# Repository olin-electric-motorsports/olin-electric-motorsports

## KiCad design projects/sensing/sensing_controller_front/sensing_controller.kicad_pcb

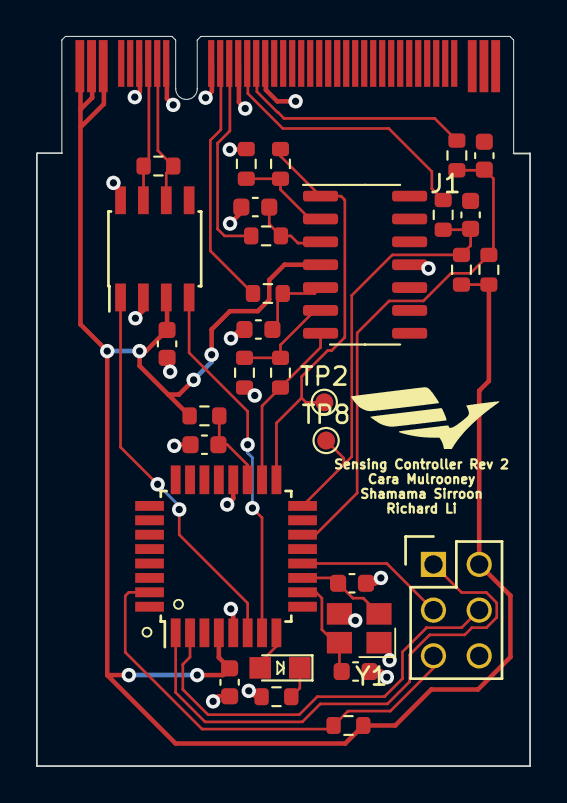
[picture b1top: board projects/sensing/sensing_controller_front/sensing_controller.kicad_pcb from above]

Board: 2 copper layers, 27.4 x 40.5 mm, 32 parts (0 on the bottom side), 27 nets.

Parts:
C1, C3, C6, C8, C9, C10: C_0.1uF; C_0603
C2: C_100pF; C_0603
C4, C5: C_30pF; C_0603
D1: LED_0805; LED_0805_OEM
J1: Automotive_M.2_Edge_Connector
J2: CONN_02X03; Pin_Header_Straight_2x03
R1, R4, R6, R14: R_100; R_0603
R2: R_120_DNP; R_0603
R3: R_10K; R_0603
R5, R11: R_200; R_0603
R7, R8, R9, R10: 100R; R_0603
R12, R13: R_1000_DNP; R_0603
TP2, TP8: TestPoint; TestPoint_Pad_D1.0mm
U1: MCP2561-E_SN; SOIC-8_3.9x4.9mm_Pitch1.27mm_OEM
U2: ATMEGA16M1; TQFP-32_7x7mm_Pitch0.8mm
U4: AD8630; SOIC-14_3.9x8.7mm_P1.27mm
Y1: Crystal_SMD; Crystal_SMD_FA238

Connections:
+5V: C1.1, C3.1, J1.P1, J1.P2, J1.P3, J2.2, R1.1, R3.1, R12.2, R13.2, U1.3 (VDD), U2.4 (VCC), U4.4 (V+)
/CAN_+: J1.7, R2.1, U1.7 (CANH)
/CAN_-: J1.8, R2.2, U1.6 (CANL)
/CAN_RX: U1.4 (RXD), U2.7 ((PCINT11/T1/ICP1B/RXCAN)PC3)
/CAN_TX: U1.1 (TXD), U2.6 ((PCINT10/T0/TXCAN)PC2)
/DEBUG_LED: D1.2 (A), U2.8 ((PCINT0/MISO/PSCOUT2A)PB0)
/MISO: J2.1, U2.1 ((PCINT18/PSCIN2/OC1A/MISO_A)PD2)
/MOSI: J2.4, U2.2 ((PCINT19/TXD/TXLIN/OC0A/~SS/MOSI_A)PD3)
/RESET: J2.5, R3.2, U2.31 ((PCINT24/OCD/~RESET)PE0)
/SCK: J2.3, U2.12 ((PCINT20/ADC1/RXD/RXLIN/ICP1A/SCK_A)PD4)
/lp1_Vout: J1.11, R8.1
/lp1_fVout: R14.1, U2.18 ((PCINT13/ADC9/ACMP3/AMP1+)PC5), U4.7
/lp2_Vout: J1.12, R7.1
/lp2_fVout: R6.1, TP2.1, U2.17 ((PCINT12/ADC8/ACMPN3/AMP1-)PC4), U4.1
/ws1_Vout: J1.14, R10.1
/ws1_fVout: C10.1, R10.2, R13.1, TP8.1, U2.16 ((PCINT2/ADC5/INT1/ACMPN0)PB2)
/ws2_Vout: J1.15, R9.1
/ws2_fVout: C9.1, R9.2, R12.1, U2.14 ((PCINT22/ADC3/INT0/ACMPN2)PD6)
GND: C1.2, C2.2, C3.2, C4.2, C5.2, C6.2, C8.2, C9.2, C10.2, J1.6, J1.9, J1.10, J1.13, J1.16, J2.6, R4.2, R5.1, R11.1, U1.2 (VSS), U1.8 (STBY), U2.5 (GND), U2.20 (AGND), U4.11 (V-), Y1.2, Y1.4
unnamed: C2.1, R1.2, U2.19 (AVCC)
unnamed: C4.1, U2.11 ((PCINT26/ADC0/XTAL2)PE2), Y1.1
unnamed: C5.1, U2.10 ((PCINT25/OC0B/XTAL1)PE1), Y1.3
unnamed: C6.1, R7.2, U4.3 (+)
unnamed: C8.1, R8.2, U4.5 (+)
unnamed: D1.1 (K), R4.1
unnamed: R5.2, R6.2, U4.2 (-)
unnamed: R11.2, R14.2, U4.6 (-)

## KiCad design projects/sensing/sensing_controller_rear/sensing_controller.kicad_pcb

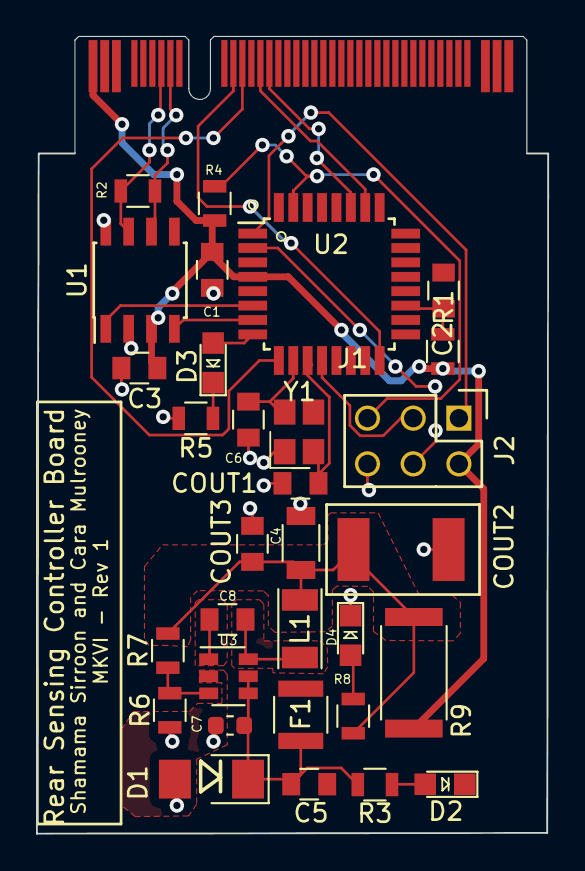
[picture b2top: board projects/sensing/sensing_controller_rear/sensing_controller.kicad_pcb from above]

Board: 2 copper layers, 28.4 x 44.3 mm, 32 parts (0 on the bottom side), 26 nets.

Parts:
C1, C3, C5, C8: C_0.1uF; C_0805_OEM
C2: C_100pF; C_0805_OEM
C4, C6: C_30pF; C_0805_OEM
C7: C_2.2uF; C_0603_1608Metric
COUT1: C_22uF; C_1206_OEM
COUT2: C_33uF; Fuse_1812
COUT3: C_47uF; C_0805_OEM
D1: D_Zener_18V; DO-214AA
D2, D3, D4: LED_0805; LED_0805_OEM
F1: F_500mA_16V; Fuse_1210
J1: Automotive_M.2_Edge_Connector
J2: CONN_02X03; Pin_Header_Straight_2x03
L1: L_100uH; L_100uH_OEM
R1, R5: R_100; R_0805_OEM
R2: R_120_DNP; R_0805_OEM
R3: R_1K; R_0805_OEM
R4: R_10K; R_0805_OEM
R6: R_25K; R_0805_OEM
R7: R_100K; R_0805_OEM
R8: R_200; R_0805_OEM
R9: R_0_2512; R_2512_OEM
U1: MCP2561-E_SN; SOIC-8_3.9x4.9mm_Pitch1.27mm_OEM
U2: ATMEGA16M1; TQFP-32_7x7mm_Pitch0.8mm
U3: TPS560430YF; SOT-23-6_OEM
Y1: Crystal_SMD; Crystal_SMD_FA238

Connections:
+5V: C1.1, C3.1, J1.P1, J2.2, R1.1, R4.1, R9.1, U1.3 (VDD), U2.4 (VCC)
/CAN_+: J1.7, R2.1, U1.7 (CANH)
/CAN_-: J1.8, R2.2, U1.6 (CANL)
/CAN_RX: U1.4 (RXD), U2.7 ((PCINT11/T1/ICP1B/RXCAN)PC3)
/CAN_TX: U1.1 (TXD), U2.6 ((PCINT10/T0/TXCAN)PC2)
/MISO: J2.1, U2.1 ((PCINT18/PSCIN2/OC1A/MISO_A)PD2)
/MOSI: J2.4, U2.2 ((PCINT19/TXD/TXLIN/OC0A/~SS/MOSI_A)PD3)
/RESET: J2.5, R4.2, U2.31 ((PCINT24/OCD/~RESET)PE0)
/SCK: J2.3, U2.12 ((PCINT20/ADC1/RXD/RXLIN/ICP1A/SCK_A)PD4)
/lp1_Vout: J1.14, U2.26 ((PCINT5/ADC6/INT2/ACMPN1/AMP2-)PB5)
/lp2_Vout: J1.15, U2.27 ((PCINT6/ADC7/PSCOUT1B)PB6)
/ws1_Vout: J1.11, U2.16 ((PCINT2/ADC5/INT1/ACMPN0)PB2)
/ws2_Vout: J1.12, U2.9 ((PCINT1/MOSI/PSCOUT2B)PB1)
GND: C1.2, C2.2, C3.2, C4.2, C5.2, C6.2, C7.2, COUT1.2, COUT2.2, COUT3.2, D1.2 (A), D2.1 (K), D4.1 (K), J1.6, J1.9, J1.10, J1.13, J1.16, J2.6, R5.2, R6.2, U1.2 (VSS), U1.8 (STBY), U2.5 (GND), U2.20 (AGND), U3.2 (GND), Y1.2, Y1.4
unnamed: C2.1, R1.2, U2.19 (AVCC)
unnamed: C4.1, U2.11 ((PCINT26/ADC0/XTAL2)PE2), Y1.1
unnamed: C5.1, C7.1, D1.1 (K), F1.1, R3.1, U3.4 (EN), U3.5 (VIN)
unnamed: C6.1, U2.10 ((PCINT25/OC0B/XTAL1)PE1), Y1.3
unnamed: C8.1, U3.1 (CB)
unnamed: C8.2, L1.1, U3.6 (SW)
unnamed: COUT1.1, COUT2.1, COUT3.1, L1.2, R7.1, R8.1, R9.2
unnamed: D2.2 (A), R3.2
unnamed: D4.2 (A), R8.2
unnamed: D3.1 (K), R5.1
unnamed: R6.1, R7.2, U3.3 (FB)
unnamed: D3.2 (A), U2.8 ((PCINT0/MISO/PSCOUT2A)PB0)

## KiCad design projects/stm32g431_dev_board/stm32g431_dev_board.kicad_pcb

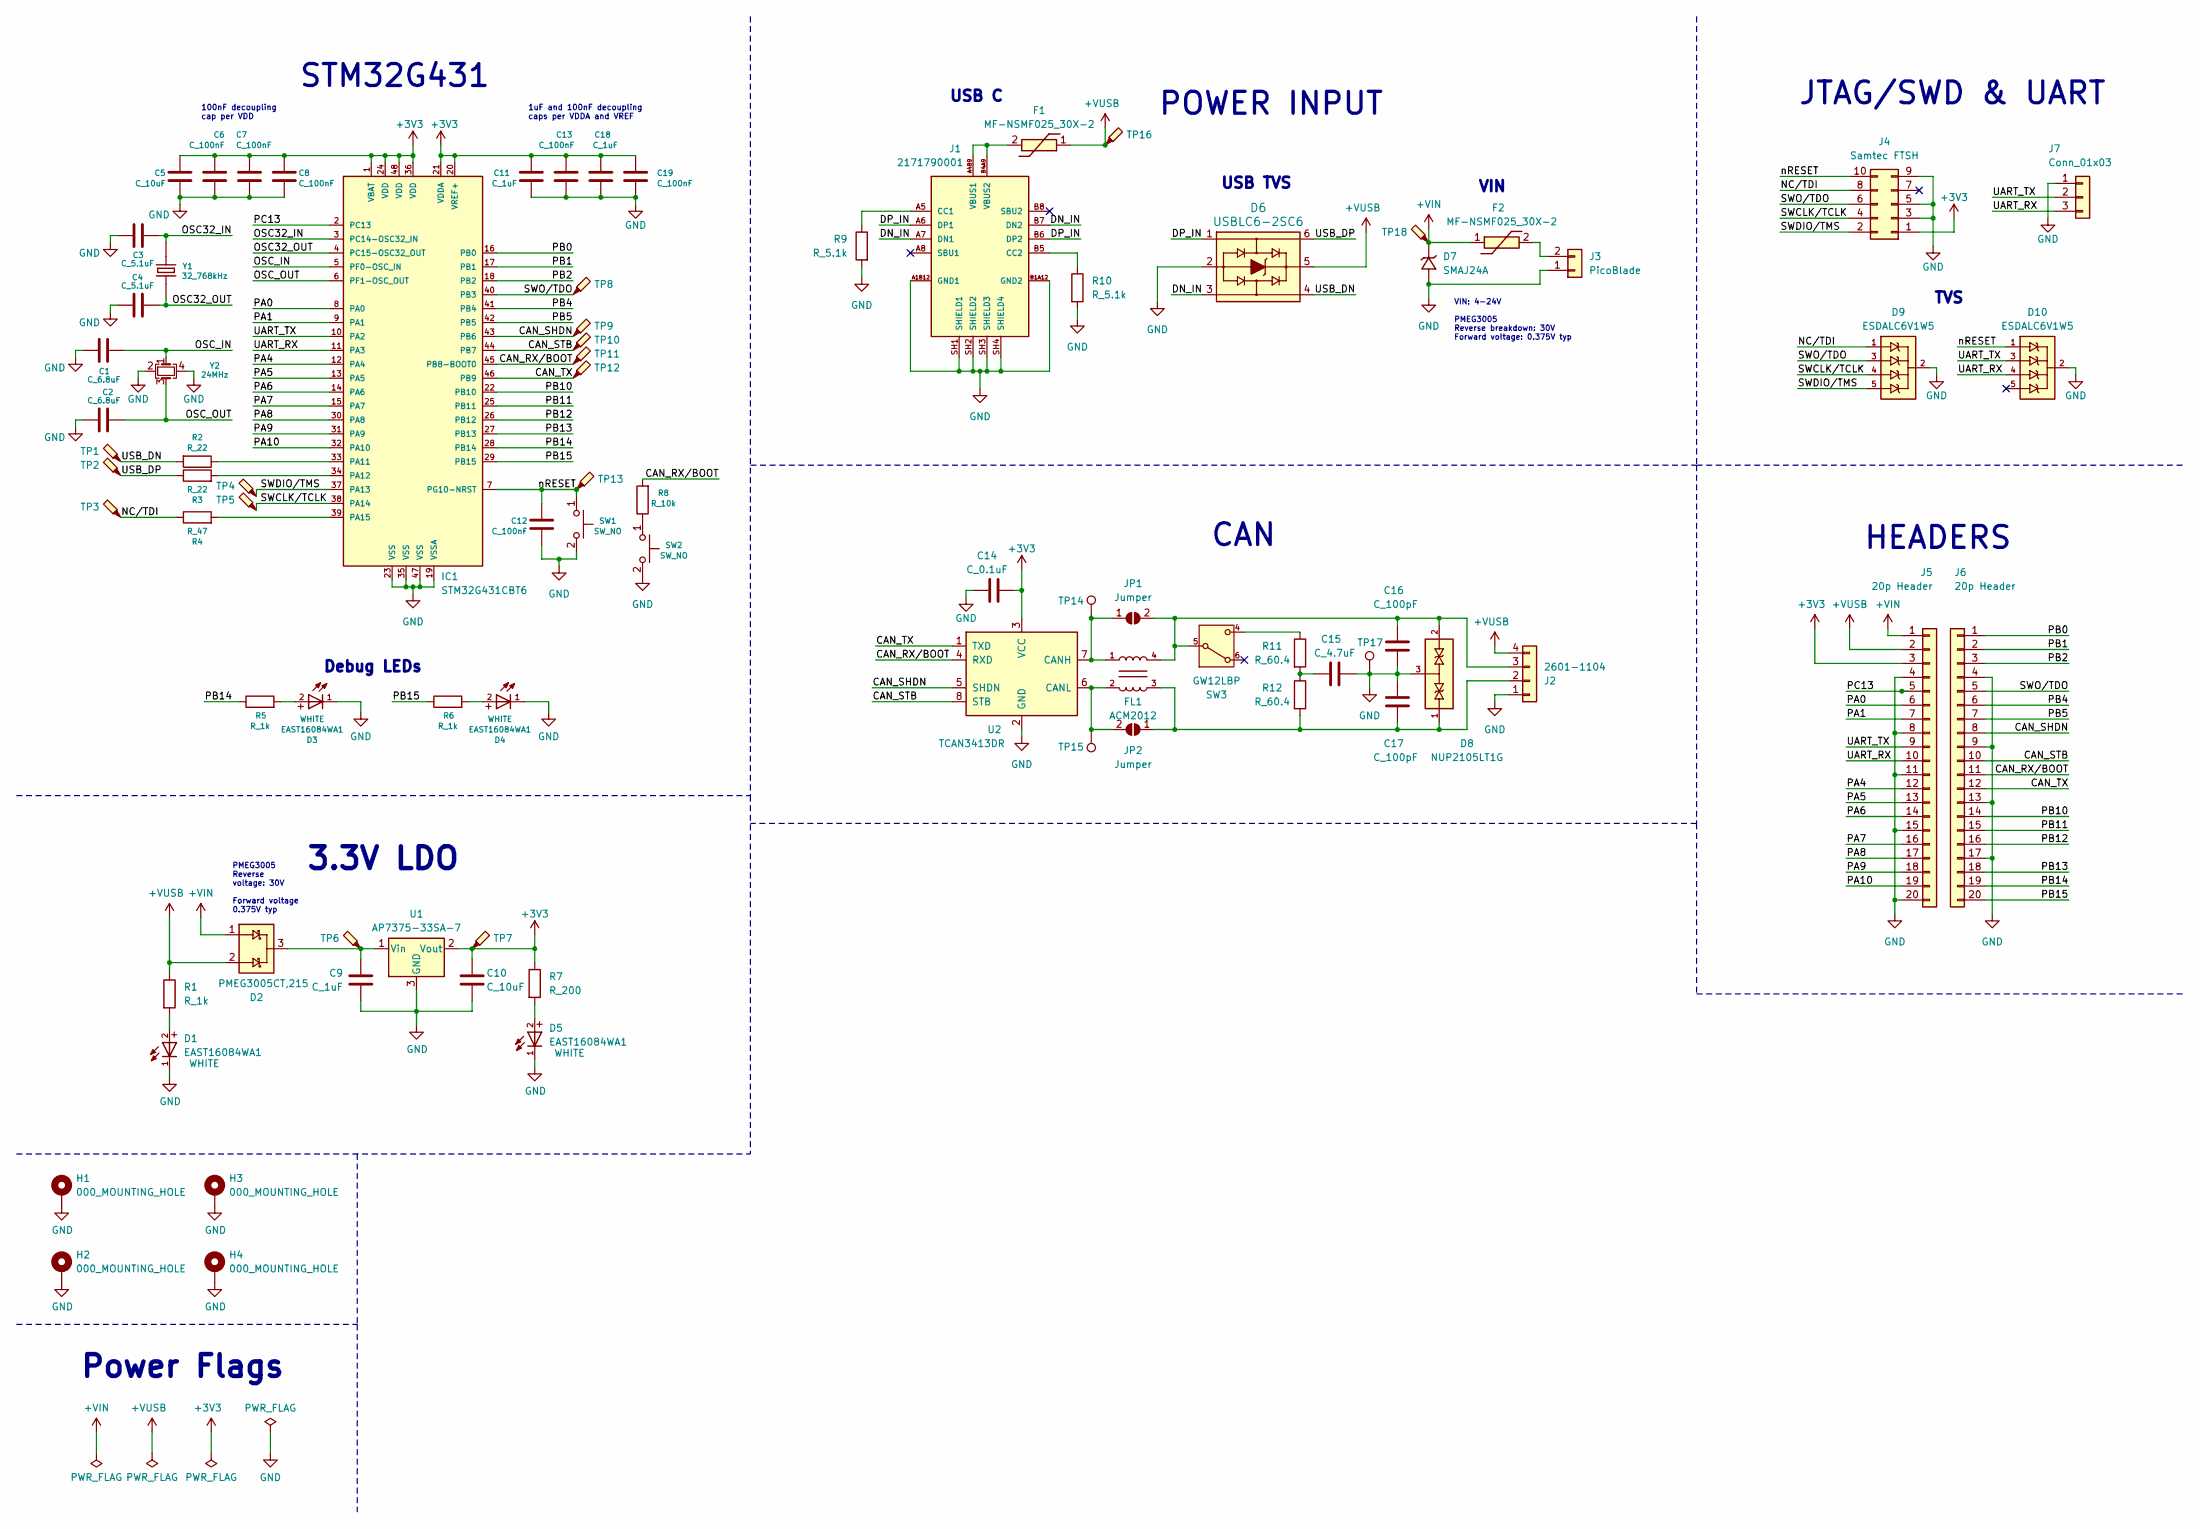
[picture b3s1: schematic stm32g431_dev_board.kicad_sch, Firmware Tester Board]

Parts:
C1, C2: C_6.8uF; C_0603_1608Metric; MPN CC0603CPNPO9BN6R8
C3, C4: C_5.1uF; C_0603_1608Metric; MPN CC0603CRNPO9BN5R1
C5, C10: C_10uF; C_0603_1608Metric; MPN LMK107BBJ106KALT
C6, C7, C8, C12, C13, C19: C_100nF; C_0603_1608Metric; MPN 1276-6717-1-ND
C9, C11, C18: C_1uF; C_0603_1608Metric; MPN CL10B105KA8NNNC
C14: C_0.1uF; C_0603_1608Metric; MPN CL10B104KB8NNWC
C15: C_4.7uF; C_0603_1608Metric; MPN 1276-1045-1-ND
C16, C17: C_100pF; C_0603_1608Metric; MPN 0603N101F101CT
D1, D3, D4, D5: EAST16084WA1; LED_0603_1608Metric; MPN EAST16084WA1
D2: PMEG3005CT,215; SOT95P237X111-3N; MPN PMEG3005CT,215
D6: USBLC6-2SC6; SOT-23-6_OEM; MPN USBLC6-2SC6
D7: SMAJ24A; SMAJ24A-13-F; MPN SMAJ24A
D8: NUP2105LT1G; SOT95P237X111-3N; MPN NUP2105LT1G
D9, D10: ESDALC6V1W5; SOT323-5L; MPN ESDALC6V1W5
F1, F2: MF-NSMF025_30X-2; MFNSMF02530X2; MPN MF-NSMF025/30X-2
FL1: ACM2012; ACM2012-201-2P-T002.kicad_mod; MPN ACM2012-201-2P-T002
H1, H2, H3, H4: 000_MOUNTING_HOLE; 000_mounting_hole
IC1: STM32G431CBT6; QFP50P900X900X160-48N; MPN STM32G431CBT6
J1: 2171790001; MOLEX_2171790001; MPN 2171790001
J2: 2601-1104; 26011104; MPN 2601-1104
J3: PicoBlade; CON_530480210_MOL
J4: Samtec FTSH; SAMTEC_FTSH-105-01-LM-D-K
J5, J6: 20p Header; PinHeader_1x20_P2.54mm_Vertical
J7: Conn_01x03; PinHeader_1x03_P2.54mm_Vertical
JP1, JP2: Jumper; SolderJumper-2_Open_Hooks0.8x1.8mm
R1, R5, R6: R_1k; R_0603_1608Metric; MPN RMCF0603FT1K00
R2, R3: R_22; R_0603_1608Metric; MPN RMCF0603FT22R0
R4: R_47; R_0603_1608Metric; MPN RMCF0603FT47R0
R7: R_200; R_0603_1608Metric; MPN RMCF0603FT200R
R8: R_10k; R_0603_1608Metric; MPN RMCF0603FT10K0
R9, R10: R_5.1k; R_0603_1608Metric; MPN RMCF0603FT5K10
R11, R12: R_60.4; R_0603_1608Metric; MPN RMCF0603FT60R4
SW1, SW2: SW_NO; SW_B3U-1000P_4.2x1.7mm; MPN SW1020CT-ND
SW3: GW12LBP; MPN GW12LBP
TP1, TP2, TP3, TP4, TP5, TP6, TP7, TP8, TP9, TP10, TP11, TP12, TP13, TP16, TP18: TestPoint_Probe; TestPoint_Hole_D1mm
TP14, TP17: CANH; TestPoint_Keystone_5000-5004_Miniature
TP15: CANL; TestPoint_Keystone_5000-5004_Miniature
U1: AP7375-33SA-7; AP7375-33SA-7_DIO; MPN AP7375-33SA-7
U2: TCAN3413DR; SOIC-8_3.9x4.9mm_Pitch1.27mm_OEM; MPN TCAN3414DR
Y1: 32_768kHz; XTAL_MU00525_NDK; MPN MU00525-32.768K
Y2: 24MHz; OSC_NX2016SA-24MHZ-EXS00A-CS10820; MPN CS10820-24M

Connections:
+3V3: C5.1, C6.1, C7.1, C8.1, C10.1, C11.1, C13.1, C14.1, C18.1, C19.1, IC1.1 (VBAT), IC1.20 (VREF+), IC1.21 (VDDA), IC1.24 (VDD), IC1.36 (VDD), IC1.48 (VDD), J4.1, J5.3, R7.1, TP7.1, U1.2 (Vout), U2.3 (VCC)
+VIN: D2.1, D7.1 (A1), F2.1, J5.1, TP18.1
+VUSB: D2.2, D6.5, F1.1, J2.4, J5.2, R1.1, TP16.1
/CAN_RX/BOOT: IC1.45 (PB8-BOOT0), J6.11, R8.2, TP11.1, U2.4 (RXD)
/CAN_SHDN: IC1.43 (PB6), J6.8, TP9.1, U2.5 (SHDN)
/CAN_STB: IC1.44 (PB7), J6.10, TP10.1, U2.8 (STB)
/CAN_TX: IC1.46 (PB9), J6.12, TP12.1, U2.1 (TXD)
/DN_IN: D6.3, J1.A7 (DN1), J1.B7 (DN2)
/DP_IN: D6.1, J1.A6 (DP1), J1.B6 (DP2)
/NC/TDI: D9.1, J4.8, R4.1, TP3.1
/OSC32_IN: C3.1, IC1.3 (PC14-OSC32_IN), Y1.2
/OSC32_OUT: C4.2, IC1.4 (PC15-OSC32_OUT), Y1.1
/OSC_IN: C1.2, IC1.5 (PF0-OSC_IN), Y2.1
/OSC_OUT: C2.2, IC1.6 (PF1-OSC_OUT), Y2.3
/PA0: IC1.8 (PA0), J5.6
/PA1: IC1.9 (PA1), J5.7
/PA4: IC1.12 (PA4), J5.12
/PA5: IC1.13 (PA5), J5.13
/PA6: IC1.14 (PA6), J5.14
/PA7: IC1.15 (PA7), J5.16
/PA8: IC1.30 (PA8), J5.17
/PA9: IC1.31 (PA9), J5.18
/PA10: IC1.32 (PA10), J5.19
/PB0: IC1.16 (PB0), J6.1
/PB1: IC1.17 (PB1), J6.2
/PB2: IC1.18 (PB2), J6.3
/PB4: IC1.41 (PB4), J6.6
/PB5: IC1.42 (PB5), J6.7
/PB10: IC1.22 (PB10), J6.14
/PB11: IC1.25 (PB11), J6.15
/PB12: IC1.26 (PB12), J6.16
/PB13: IC1.27 (PB13), J6.18
/PB14: IC1.28 (PB14), J6.19, R5.1
/PB15: IC1.29 (PB15), J6.20, R6.1
/PC13: IC1.2 (PC13), J5.5
/SWCLK/TCLK: D9.4, IC1.38 (PA14), J4.4, TP5.1
/SWDIO/TMS: D9.5, IC1.37 (PA13), J4.2, TP4.1
/SWO/TDO: D9.3, IC1.40 (PB3), J4.6, J6.5, TP8.1
/UART_RX: D10.4, IC1.11 (PA3), J5.10, J7.3
/UART_TX: D10.3, IC1.10 (PA2), J5.9, J7.2
/USB_DN: D6.4, R2.2, TP1.1
/USB_DP: D6.6, R3.1, TP2.1
/nRESET: C12.1, D10.1, IC1.7 (PG10-NRST), J4.10, SW1.1, TP13.1
GND: C1.1, C2.1, C3.2, C4.1, C5.2, C6.2, C7.2, C8.2, C9.2, C10.2, C11.2, C12.2, C13.2, C14.2, C15.2, C16.2, C17.1, C18.2, C19.2, D1.1, D3.1, D4.1, D5.1, D6.2, D7.2 (A2), D8.3, D9.2, D10.2, H1.1, H2.1, H3.1, H4.1, IC1.19 (VSSA), IC1.23 (VSS), IC1.35 (VSS), IC1.47 (VSS), J1.A1B12 (GND1), J1.B1A12 (GND2), J1.SH1 (SHIELD1), J1.SH2 (SHIELD2), J1.SH3 (SHIELD3), J1.SH4 (SHIELD4), J2.1, J3.1, J4.3, J4.5, J4.9, J5.4, J5.8, J5.11, J5.15, J5.20, J6.4, J6.9, J6.13, J6.17, J7.1, R9.2, R10.2, SW1.2, SW2.2, TP17.1, U1.3 (GND), U2.2 (GND), Y2.2, Y2.4
unnamed: C15.1, R11.2, R12.1
unnamed: D1.2, R1.2
unnamed: D3.2, R5.2
unnamed: D4.2, R6.2
unnamed: D5.2, R7.2
unnamed: IC1.33 (PA11), R2.1
unnamed: IC1.34 (PA12), R3.2
unnamed: IC1.39 (PA15), R4.2
unnamed: J1.A5 (CC1), R9.1
unnamed: J1.B5 (CC2), R10.1
unnamed: F1.2, J1.A4B9 (VBUS1), J1.B4A9 (VBUS2)
unnamed: F2.2, J3.2
unnamed: FL1.1, JP1.1 (A), TP14.1, U2.7 (CANH)
unnamed: C16.1, D8.2, FL1.4, J2.3, JP1.2 (B), SW3.5
unnamed: C17.2, D8.1, FL1.3, J2.2, JP2.1 (A), R12.2
unnamed: FL1.2, JP2.2 (B), TP15.1, U2.6 (CANL)
unnamed: R8.1, SW2.1
unnamed: R11.1, SW3.4
unnamed: C9.1, D2.3, TP6.1, U1.1 (Vin)

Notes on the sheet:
3.3V LDO
USB C
CAN
VIN
1uF and 100nF decoupling caps per VDDA and VREF
PMEG3005 Reverse voltage: 30V Forward voltage 0.375V typ
Power Flags
JTAG/SWD & UART
Debug LEDs
HEADERS
100nF decoupling cap per VDD
USB TVS
VIN: 4-24V PMEG3005 Reverse breakdown: 30V Forward voltage: 0.375V typ
STM32G431
TVS
POWER INPUT

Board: 2 copper layers, 123 parts (4 on the bottom side), 63 nets, no tracks yet.

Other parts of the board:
kibuzzard-670C7F9E: G***; kibuzzard-670C7F9E
kibuzzard-670C85A1: G***; kibuzzard-670C85A1
kibuzzard-670C85A5: G***; kibuzzard-670C85A5
kibuzzard-670C86B2: G***; kibuzzard-670C86B2
kibuzzard-670C86B8: G***; kibuzzard-670C86B8
kibuzzard-670C86BC: G***; kibuzzard-670C86BC
kibuzzard-670C86C0: G***; kibuzzard-670C86C0
kibuzzard-670C86C5: G***; kibuzzard-670C86C5
kibuzzard-670C86CA: G***; kibuzzard-670C86CA
kibuzzard-670C86CE: G***; kibuzzard-670C86CE
kibuzzard-670C86D3: G***; kibuzzard-670C86D3
kibuzzard-670C86D7: G***; kibuzzard-670C86D7
kibuzzard-670C86DC: G***; kibuzzard-670C86DC
kibuzzard-670C86E5: G***; kibuzzard-670C86E5
kibuzzard-670C86E9: G***; kibuzzard-670C86E9
kibuzzard-670C854F: G***; kibuzzard-670C854F
kibuzzard-670C856A: G***; kibuzzard-670C856A
kibuzzard-670C856D: G***; kibuzzard-670C856D
kibuzzard-670C857B: G***; kibuzzard-670C857B
kibuzzard-670C864A: G***; kibuzzard-670C864A
kibuzzard-670C864D: G***; kibuzzard-670C864D
kibuzzard-670C865B: G***; kibuzzard-670C865B
kibuzzard-670C866D: G***; kibuzzard-670C866D
kibuzzard-670C8553: G***; kibuzzard-670C8553
kibuzzard-670C8559: G***; kibuzzard-670C8559
kibuzzard-670C8572: G***; kibuzzard-670C8572
kibuzzard-670C8577: G***; kibuzzard-670C8577
kibuzzard-670C8580: G***; kibuzzard-670C8580
kibuzzard-670C8587: G***; kibuzzard-670C8587
kibuzzard-670C8626: G***; kibuzzard-670C8626
kibuzzard-670C8641: G***; kibuzzard-670C8641
kibuzzard-670C8654: G***; kibuzzard-670C8654
kibuzzard-670C8662: G***; kibuzzard-670C8662
kibuzzard-670C8674: G***; kibuzzard-670C8674
kibuzzard-670C8679: G***; kibuzzard-670C8679
kibuzzard-670C8682: G***; kibuzzard-670C8682
kibuzzard-670C8688: G***; kibuzzard-670C8688
kibuzzard-670C8690: G***; kibuzzard-670C8690
kibuzzard-670C8694: G***; kibuzzard-670C8694
kibuzzard-670C8698: G***; kibuzzard-670C8698

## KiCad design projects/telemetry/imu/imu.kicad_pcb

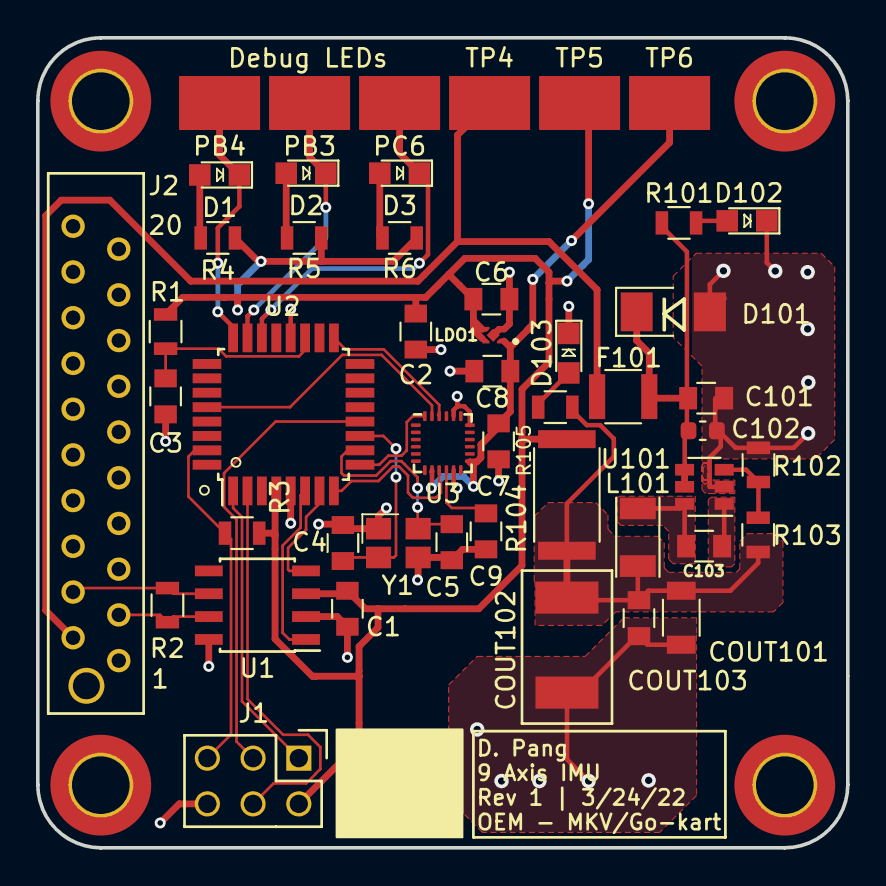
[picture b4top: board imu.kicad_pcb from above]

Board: 2 copper layers, 45.0 x 45.0 mm, 48 parts (0 on the bottom side), 33 nets.

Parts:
C1, C2, C7, C9, C101, C103: C_0.1uF; C_0805_OEM
C3: C_100pF; C_0805_OEM
C4, C5: C_30pF; C_0805_OEM
C6, C8: C_1uF; C_0805_OEM
C102: C_2.2uF; C_0603_1608Metric
COUT101: C_22uF; C_1206_OEM
COUT102: C_33uF; Fuse_1812
COUT103: C_47uF; C_0805_OEM
D1, D2, D3, D102, D103: LED_0805; LED_0805_OEM
D101: D_Zener_18V; DO-214AA
F101: F_500mA_16V; Fuse_1210
J1: CONN_02X03; Pin_Header_Straight_2x03
J2: MM_F_VT_20; micromatch_female_vert_20
L101: L_100uH; L_100uH_OEM
LDO1: NCP110AMX180TBG; XDFN4
PB3, PB4: Test_Point_SMD
PC6: Test_Point_SMD
R1: R_100; R_0805_OEM
R2: R_120_DNP; R_0805_OEM
R3: R_10K; R_0805_OEM
R4, R5, R6: R_499; R_0805_OEM
R101: R_1K; R_0805_OEM
R102: R_25K; R_0805_OEM
R103: R_100K; R_0805_OEM
R104: R_0_2512; R_2512_OEM
R105: R_200; R_0805_OEM
TP4, TP5, TP6: Test_Point_SMD
U1: MCP2561-E_SN; SOIC-8_3.9x4.9mm_Pitch1.27mm_OEM
U2: ATMEGA16M1; TQFP-32_7x7mm_Pitch0.8mm
U3: ICM-20948; InvenSense_QFN-24_3x3mm_P0.4mm
U101: TPS560430YF; SOT-23-6_OEM
Y1: Crystal_SMD; Crystal_SMD_FA238

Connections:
+1V8: C7.1, C8.1, LDO1.1, TP6.1, U3.8, U3.13
+5V: C1.1, C2.1, C6.1, J1.2, LDO1.3, LDO1.4, R1.1, R3.1, R4.2, R5.2, R6.2, R104.1, TP5.1, U1.3, U2.4
+BATT: F101.2, J2.2, TP4.1
/CAN_+: J2.3, R2.1, U1.7
/CAN_-: J2.4, R2.2, U1.6
/CAN_RX: U1.4, U2.7
/CAN_TX: U1.1, U2.6
/CS: U2.17, U3.22
/MISO: U2.8, U3.9
/MISO_A: J1.1, U2.1
/MOSI: U2.9, U3.24
/MOSI_A: J1.4, U2.2
/P_LED1: D1.1, PB4.1, U2.24
/P_LED2: D2.1, PB3.1, U2.23
/P_LED3: D3.1, PC6.1, U2.22
/RESET: J1.5, R3.2, U2.31
/SCK: U2.28, U3.23
/SCK_A: J1.3, U2.12
GND: C1.2, C2.2, C3.2, C4.2, C5.2, C6.2, C7.2, C8.2, C9.1, C101.2, C102.2, COUT101.2, COUT102.2, COUT103.2, D101.2, D102.1, D103.1, J1.6, J2.1, J2.5, J2.6, J2.7, J2.8, J2.9, J2.10, J2.11, J2.12, J2.13, J2.14, J2.15, J2.16, J2.17, J2.18, J2.19, J2.20, LDO1.2, R102.2, U1.2, U1.8, U2.5, U2.20, U3.11, U3.18, U3.20, U101.2, Y1.2, Y1.4
unnamed: C3.1, R1.2, U2.19
unnamed: C4.1, U2.11, Y1.1
unnamed: C5.1, U2.10, Y1.3
unnamed: C9.2, U3.10
unnamed: C101.1, C102.1, D101.1, F101.1, R101.1, U101.4, U101.5
unnamed: C103.1, U101.1
unnamed: C103.2, L101.1, U101.6
unnamed: COUT101.1, COUT102.1, COUT103.1, L101.2, R103.1, R104.2, R105.1
unnamed: D1.2, R4.1
unnamed: D2.2, R5.1
unnamed: D3.2, R6.1
unnamed: D102.2, R101.2
unnamed: D103.2, R105.2
unnamed: R102.1, R103.2, U101.3

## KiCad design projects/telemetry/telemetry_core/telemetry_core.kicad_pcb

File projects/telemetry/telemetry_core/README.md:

See [Coda Page](https://coda.io/d/_dLTyp9cQyXS/RF-Telemetry-System_suVogLCA) for detailed documentation.

Brief Setup

1. Navigate to the OEM’s git repository

```cd Documents/olin-electric-motorsports # Might be different on your machine```bash

2. Start the telemetry server and telemetry canviewer

```bazel run //projects/telemetry/telemetry_core```bash

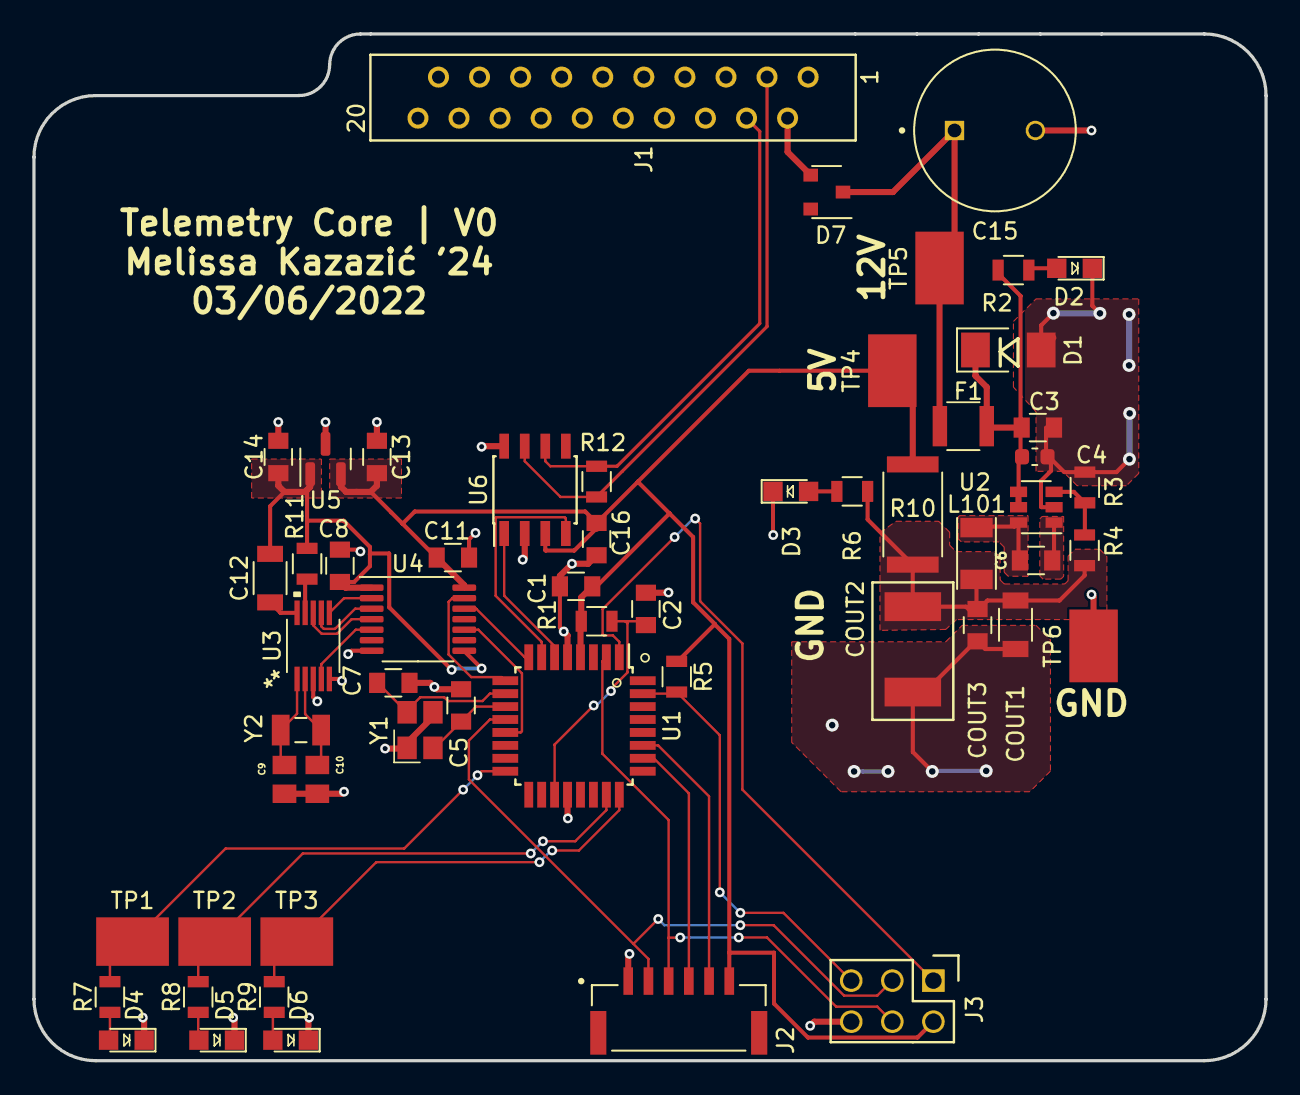
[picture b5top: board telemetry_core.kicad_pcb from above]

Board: 2 copper layers, 76.2 x 63.5 mm, 57 parts (0 on the bottom side), 42 nets.

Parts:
C1, C3, C6, C8, C11, C13, C14, C16: C_0.1uF; C_0805_OEM
C2: C_100pF; C_0805_OEM
C4: C_2.2uF; C_0603_1608Metric
C5, C7: C_30pF; C_0805_OEM
C9, C10: C_10pF; C_10pf
C12: C_10nF; C_1206_OEM
C15: C_radial_10mm_5mm
COUT1: C_22uF; C_1206_OEM
COUT2: C_33uF; Fuse_1812
COUT3: C_47uF; C_0805_OEM
D1: D_Zener_18V; DO-214AA
D2, D3, D4, D5, D6: LED_0805; LED_0805_OEM
D7: BAT400D-7-F; SOT-23-3_OEM
F1: F_500mA_16V; Fuse_1210
J1: MM_F_RA_20; micromatch_female_ra_20
J2: JST_SM06B-GHS-TB_LF__SN_
J3: CONN_02X03; Pin_Header_Straight_2x03
L101: L_100uH; L_100uH_OEM
R1: R_100; R_0805_OEM
R2: R_1K; R_0805_OEM
R3: R_25K; R_0805_OEM
R4: R_100K; R_0805_OEM
R5: R_10K; R_0805_OEM
R6, R7, R8, R9: R_200; R_0805_OEM
R10: R_0_2512; R_2512_OEM
R11: R_475; R_0805_OEM
R12: R_120_DNP; R_0805_OEM
TP1, TP2, TP3, TP4, TP5, TP6: Test_Point_SMD
U1: ATMEGA16M1; TQFP-32_7x7mm_Pitch0.8mm
U2: TPS560430YF; SOT-23-6_OEM
U3: MCP79511-I_MS; MCP79511_I_MS
U4: TXB0104PW; TSSOP-14_4.4x5mm_P0.65mm
U5: LM3480-3.3; SOT-23
U6: MCP2561-E_SN; SOIC-8_3.9x4.9mm_Pitch1.27mm_OEM
Y1: Crystal_SMD; Crystal_SMD_FA238
Y2: Crystal_32_768kHz; Crystal_32_768kHZ

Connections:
+3V3: C8.2, C12.1, C14.1, R11.1, U4.1, U4.8, U5.1
+5V: C1.1, C11.1, C13.1, C16.1, J2.6, J3.2, R1.1, R5.1, R10.1, TP4.1, U1.4, U4.14, U5.2, U6.3
/12V: C15.P, D7.1, F1.2, TP5.1
/12V_IN: D7.2, J1.2
/CAN_N: J1.4, R12.2, U6.6
/CAN_P: J1.3, R12.1, U6.7
/CAN_RX: U1.7, U6.4
/CAN_TX: U1.6, U6.1
/CSB: U1.13, U4.10
/CSB_RTC: U3.4, U4.5
/CTS_RADIO: J2.4, U1.26
/MISO: J3.1, U1.1
/MOSI: J2.3, J3.4, U1.2
/P_LED_1: R7.2, TP1.1, U1.16
/P_LED_2: R8.2, TP2.1, U1.23
/P_LED_3: R9.2, TP3.1, U1.24
/RESET: J3.5, R5.2, U1.31
/RTS_RADIO: J2.5, U1.27
/RXD_RADIO: J2.2, J3.3, U1.12
/SCK_RTC: U3.8, U4.4
/SI_ATMEGA: U1.9, U4.13
/SI_RTC: U3.6, U4.2
/SO_ATMEGA: U1.8, U4.12
/SO_RTC: U3.7, U4.3
GND: C1.2, C2.2, C3.2, C4.2, C5.2, C7.2, C8.1, C9.2, C10.2, C11.2, C13.2, C14.2, C15.N, C16.2, COUT1.2, COUT2.2, COUT3.2, D1.2, D2.1, D3.1, D4.1, D5.1, D6.1, J1.1, J1.5, J1.6, J1.7, J1.8, J1.9, J1.10, J1.11, J1.12, J1.13, J1.14, J1.15, J1.16, J1.17, J1.18, J1.19, J1.20, J2.1, J3.6, R3.2, TP6.1, U1.5, U1.20, U2.2, U3.3, U3.5, U4.7, U5.3, U6.2, U6.8, Y1.2, Y1.4
unnamed: C2.1, R1.2, U1.19
unnamed: C3.1, C4.1, D1.1, F1.1, R2.1, U2.4, U2.5
unnamed: C5.1, U1.11, Y1.1
unnamed: C6.1, U2.1
unnamed: C6.2, L101.1, U2.6
unnamed: C7.1, U1.10, Y1.3
unnamed: C9.1, U3.1, Y2.1
unnamed: C10.1, U3.2, Y2.2
unnamed: C12.2, U3.10
unnamed: COUT1.1, COUT2.1, COUT3.1, L101.2, R4.1, R6.1, R10.2
unnamed: D2.2, R2.2
unnamed: D3.2, R6.2
unnamed: D4.2, R7.1
unnamed: D5.2, R8.1
unnamed: D6.2, R9.1
unnamed: R3.1, R4.2, U2.3
unnamed: R11.2, U3.9

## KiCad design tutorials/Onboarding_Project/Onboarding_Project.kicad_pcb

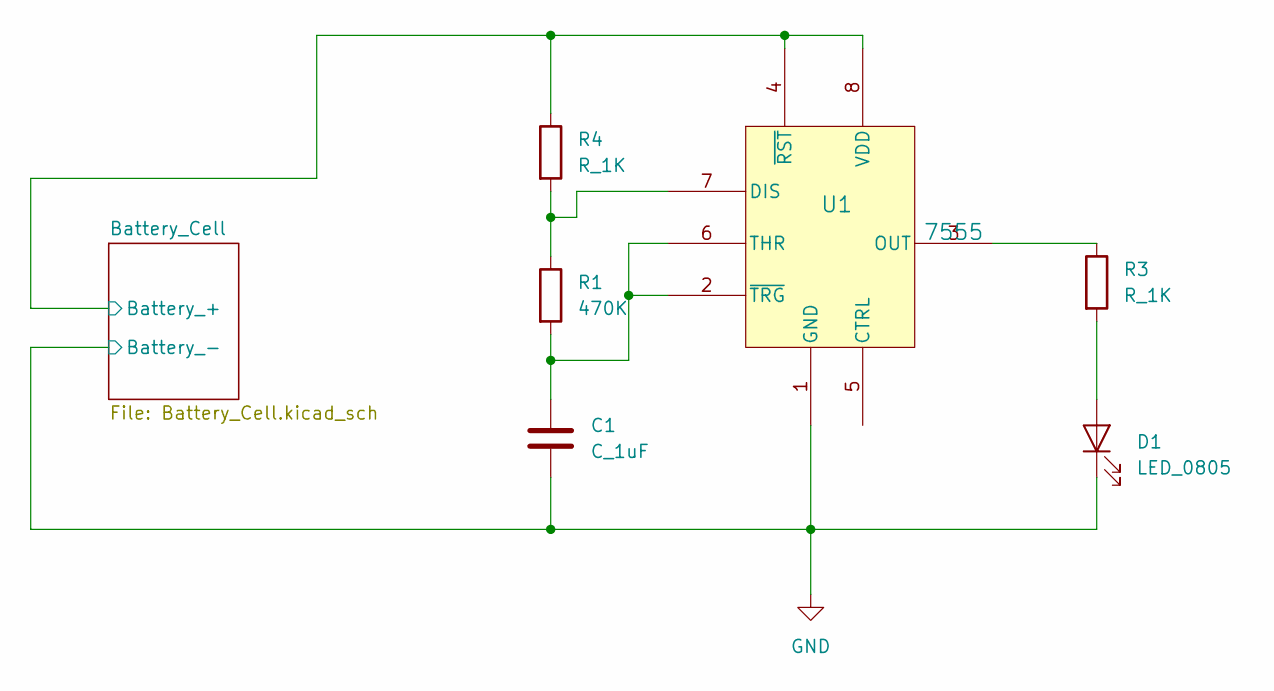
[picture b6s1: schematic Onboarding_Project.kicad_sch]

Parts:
C1: C_1uF; C_0805_OEM; MPN 1276-6470-1-ND
D1: LED_0805; LED_0805_OEM; MPN 475-1410-1-ND
R1: 470K; R_0805_OEM
R3, R4: R_1K; R_0805_OEM; MPN RNCP0805FTD1K00CT-ND
U1: 7555

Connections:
/Battery_Cell/Battery_+: R4.1, U1.4 (~RST), U1.8 (VDD); also elsewhere on the board
GND: C1.2, D1.1 (K), U1.1 (GND); also elsewhere on the board
unnamed: D1.2 (A), R3.2
unnamed: R1.1, R4.2, U1.7 (DIS)
unnamed: R3.1, U1.3 (OUT)
unnamed: C1.1, R1.2, U1.2 (~TRG), U1.6 (THR)

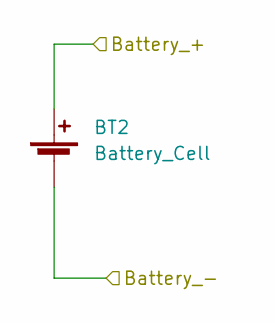
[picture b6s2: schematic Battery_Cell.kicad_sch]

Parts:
BT2: Battery_Cell; Battery Cell

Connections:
/Battery_Cell/Battery_+: BT2.1 (+), BT2.2 (-); also elsewhere on the board
GND: BT2.3; also elsewhere on the board

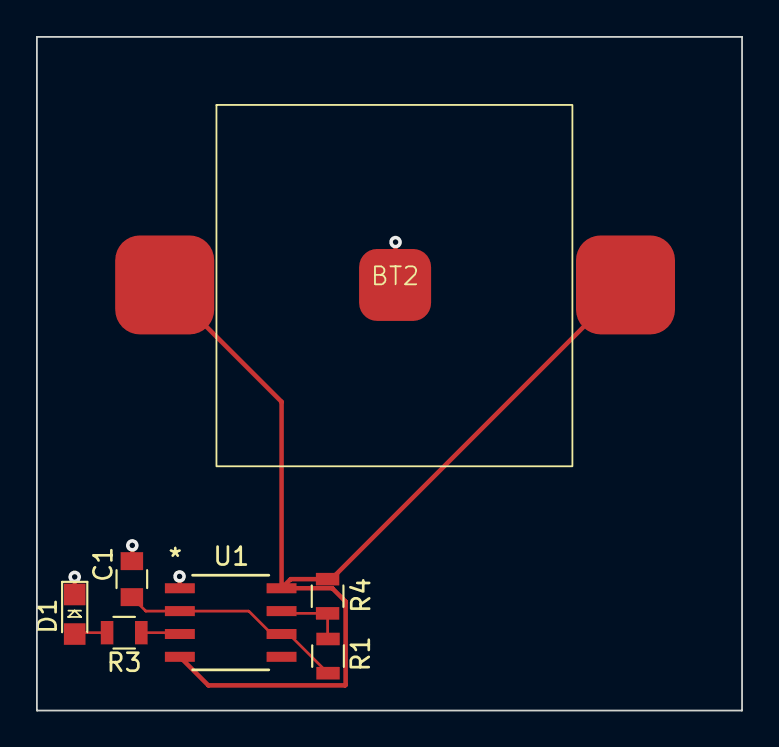
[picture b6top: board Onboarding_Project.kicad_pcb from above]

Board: 2 copper layers, 39.2 x 37.4 mm, 7 parts (0 on the bottom side), 6 nets.

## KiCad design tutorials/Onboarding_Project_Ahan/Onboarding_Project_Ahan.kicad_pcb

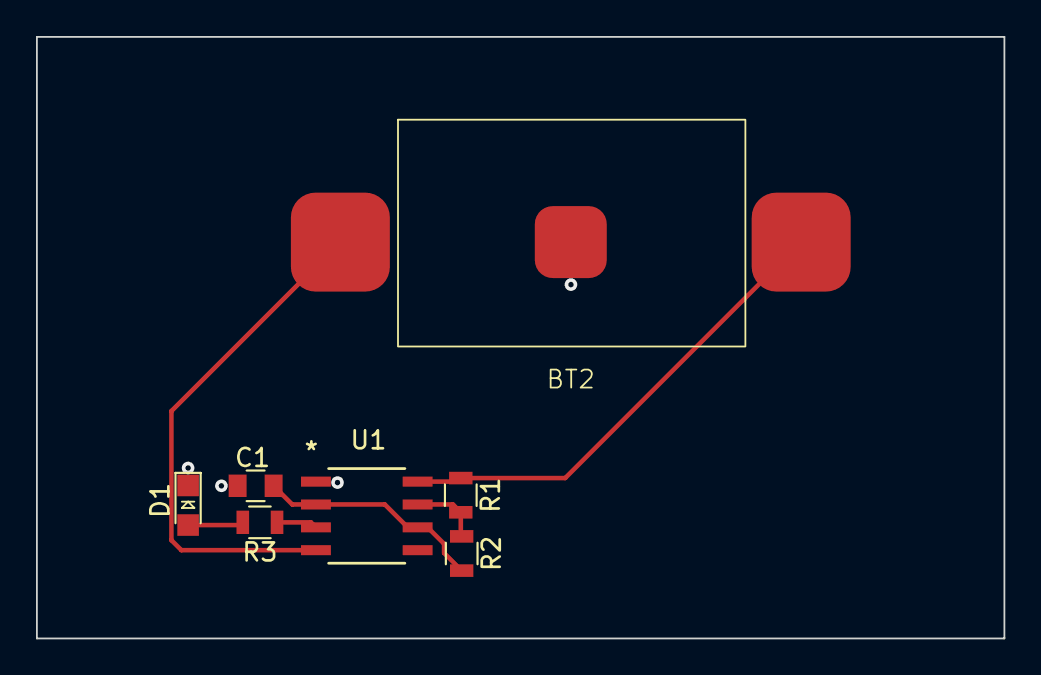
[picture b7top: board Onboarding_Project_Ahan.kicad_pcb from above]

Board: 2 copper layers, 53.8 x 33.4 mm, 7 parts (0 on the bottom side), 6 nets.

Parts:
BT2: Battery_Cell; BatteryCell
C1: C_1uF; C_0805_OEM
D1: LED; LED_0805_OEM
R1, R3: R_1K; R_0805_OEM
R2: 470k; R_0805_OEM
U1: 7555

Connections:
/Battery/Battery+: BT2.1 (+), BT2.3, R1.1, U1.4 (RST), U1.8 (VDD)
GND: BT2.2 (-), C1.2, D1.1 (K), U1.1 (GND)
unnamed: D1.2 (A), R3.2
unnamed: R1.2, R2.1, U1.7 (DISC)
unnamed: R3.1, U1.3 (OUTPUT)
unnamed: C1.1, R2.2, U1.2 (~TRG), U1.6 (THR)

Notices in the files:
parts and their libraries:
Copyright 2021 Accelerated Designs. All rights reserved.
